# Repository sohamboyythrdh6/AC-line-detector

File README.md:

i made a ac line detector from some bc547 transistor a buzzer some . I build this project for safely drill wall without puncher any live wire to prevent shock circuits and also this is very cheep

------------------------------------------------------------
| Component | Purpose | Qty | Cost (USD) | Distributor |
|-----------|----------|-----|------------|-------------|
| Battery Case | Connects the battery to the circuit | 1 | $0.48 | Maker Bazar |
| 9V Battery | Powers the circuit | 1 | $0.24 | Maker Bazar |
| Active Buzzer | Audible alert when AC voltage is detected | 1 | $0.13 | Maker Bazar |
| 5mm LED | Visual indication when AC voltage is detected | 1 | $0.26 | Maker Bazar |
| 220Ω Resistor | Limits LED current and controls brightness | 1 | $0.16 | Maker Bazar |
| BC547 Transistor | Amplifies weak AC signal to drive indicators | 3 | $0.20 | Maker Bazar |
| 1MΩ 1/4W Resistor | Biasing resistor for transistor stability | 1 | $0.16 | Maker Bazar |
| Custom PCB | Connects all components together | 1 | $2.00 | JLCPCB |
|delivery charge||2|$8.66||
-------------------------------------------------------------

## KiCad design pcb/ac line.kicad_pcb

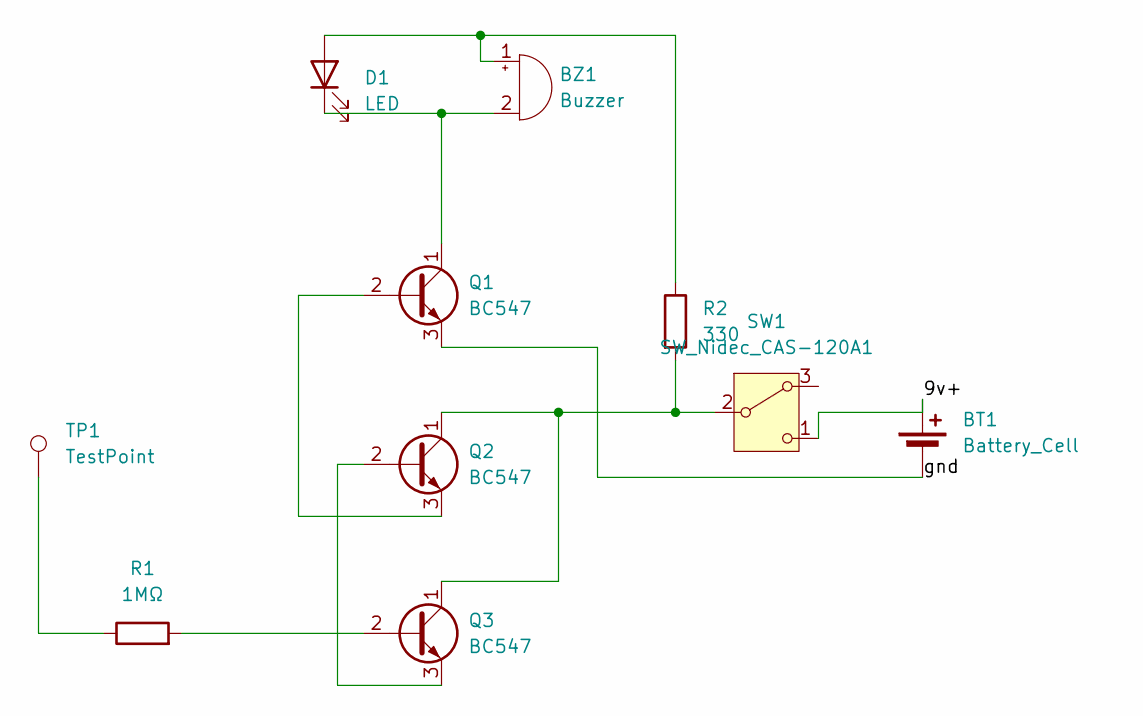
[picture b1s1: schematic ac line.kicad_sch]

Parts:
BT1: Battery_Cell; BatteryHolder_MPD_BA9VPC_1xPP3
BZ1: Buzzer; Buzzer_12x9.5RM7.6
D1: LED; LED_D5.0mm
Q1, Q2, Q3: BC547; TO-92_Inline
R1: 1MΩ; R_Axial_DIN0204_L3.6mm_D1.6mm_P5.08mm_Horizontal
R2: 330; R_Axial_DIN0204_L3.6mm_D1.6mm_P5.08mm_Horizontal
SW1: SW_Nidec_CAS-120A1; SW_Slide_SPDT_Straight_CK_OS102011MS2Q
TP1: TestPoint; TestPoint_THTPad_D2.0mm_Drill1.0mm

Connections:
/9v+: BT1.1 (+), SW1.1 (C)
/gnd: BT1.2 (-), Q1.3 (E)
unnamed: BZ1.1 (+), D1.2 (A), R2.1
unnamed: BZ1.2 (-), D1.1 (K), Q1.1 (C)
unnamed: Q1.2 (B), Q2.3 (E)
unnamed: Q2.2 (B), Q3.3 (E)
unnamed: Q2.1 (C), Q3.1 (C), R2.2, SW1.2 (B)
unnamed: Q3.2 (B), R1.2
unnamed: R1.1, TP1.1 (1_1)

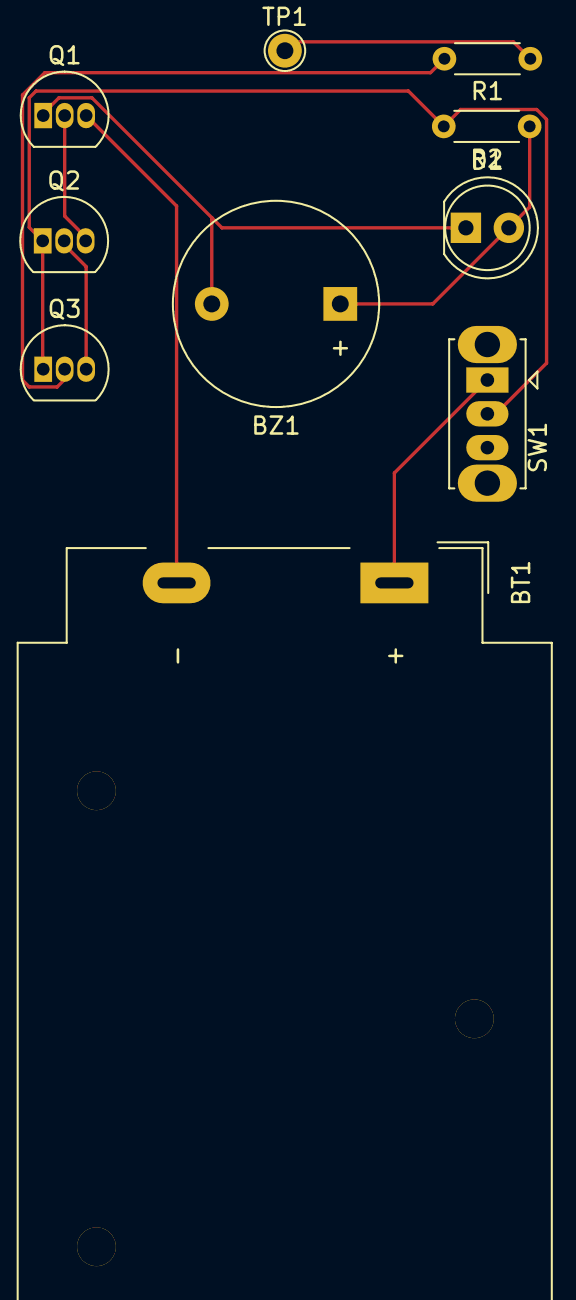
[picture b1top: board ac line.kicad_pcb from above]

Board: 2 copper layers, 10 parts (0 on the bottom side), 9 nets.

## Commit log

2026-04-07 Create assist
2026-04-08 Add new file pcb/y with initial content
2026-04-09 Create a
2026-04-09 Add Bill of Materials (BOM) for components
2026-04-11 Create 1
2026-04-11 Update BOM
2026-04-11 Fix grammar in README project description
    Corrected grammar and punctuation in project description.
2026-06-23 Refactor BOM format to CSV style
2026-06-23 Revise BOM.csv with component details and links
    Updated BOM.csv to include detailed component information and links.
